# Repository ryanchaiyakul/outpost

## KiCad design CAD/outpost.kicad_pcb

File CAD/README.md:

# CAD

KiCad schematic and board design.

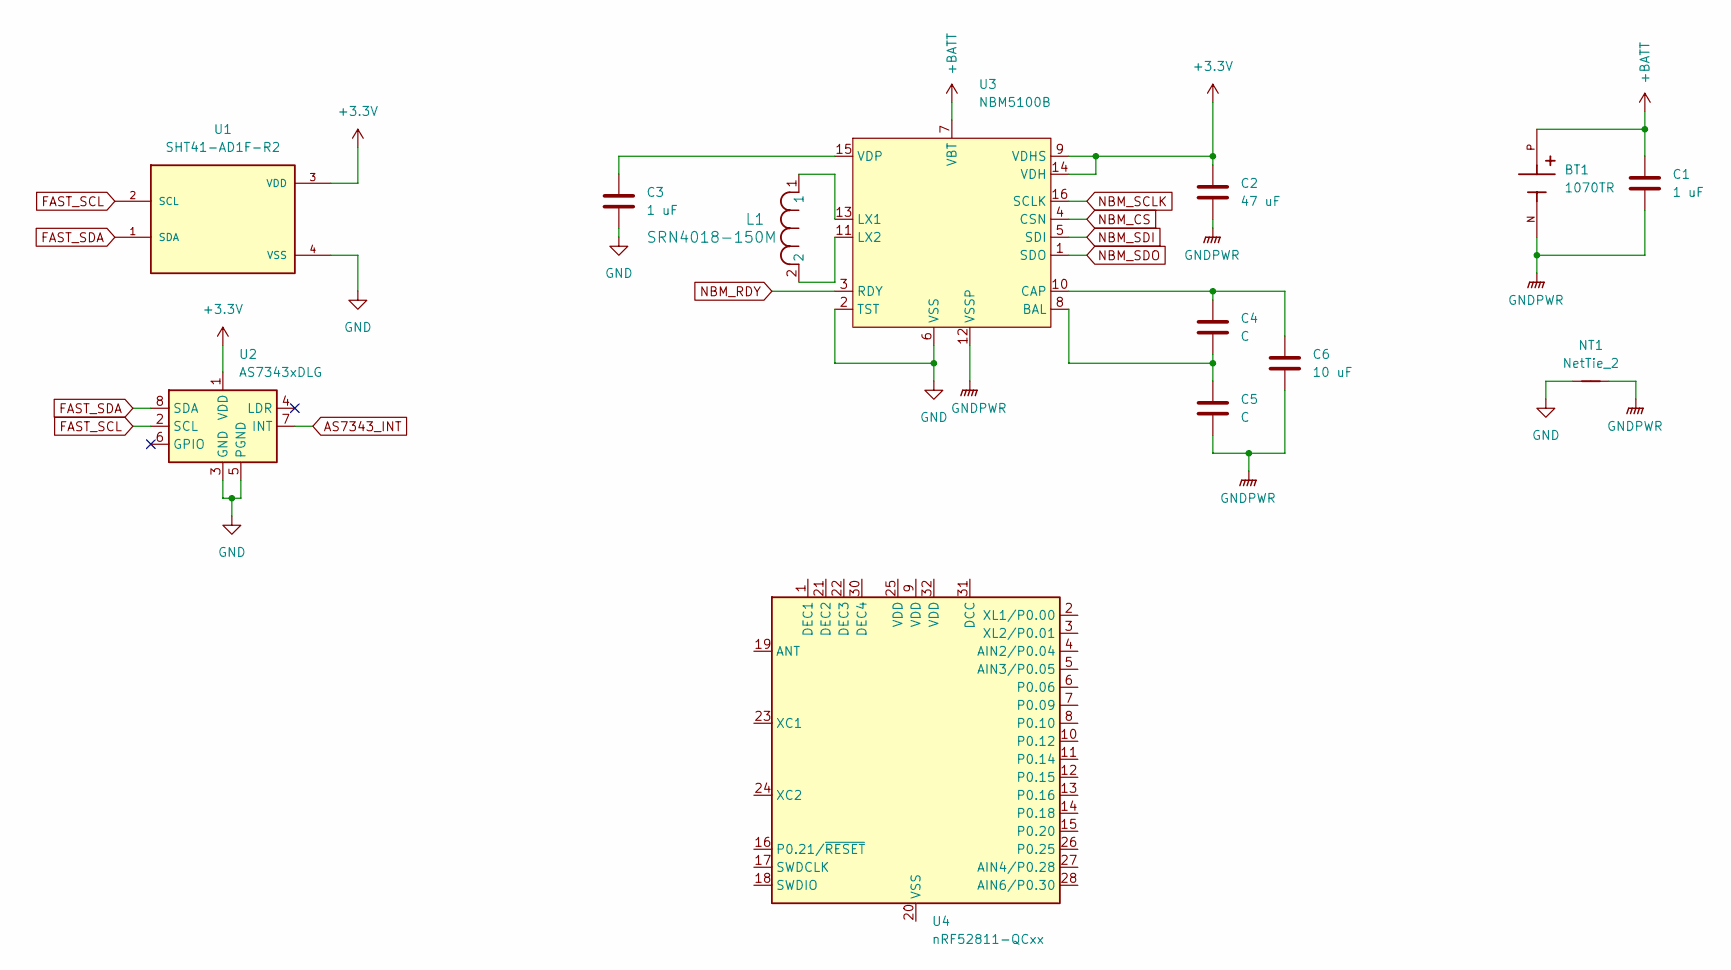
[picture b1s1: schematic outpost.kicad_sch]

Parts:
BT1: 1070TR; KEYSTONE_1070TR; PARTREV C
C1, C3: 1 uF; C_0603_1608Metric_Pad1.08x0.95mm_HandSolder
C2: 47 uF; C_0603_1608Metric_Pad1.08x0.95mm_HandSolder
C4, C5: C; C_0603_1608Metric_Pad1.08x0.95mm_HandSolder
C6: 10 uF; C_0603_1608Metric_Pad1.08x0.95mm_HandSolder
L1: SRN4018-150M; IND_BOURNS_SRN4018
NT1: NetTie_2; NetTie-2_THT_Pad1.0mm
U1: SHT41-AD1F-R2; SHT4X
U2: AS7343xDLG; AMS_OLGA-8_2x3.1mm_P0.8mm
U3: NBM5100B; SOT763-1
U4: nRF52811-QCxx; QFN-32-1EP_5x5mm_P0.5mm_EP3.6x3.6mm_ThermalVias

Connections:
+3.3V: C2.1, U1.3 (VDD), U2.1 (VDD), U3.9 (VDHS), U3.14 (VDH)
+BATT: BT1.P, C1.1, U3.7 (VBT)
AS7343_INT: U2.7 (INT)
FAST_SCL: U1.2 (SCL), U2.2 (SCL)
FAST_SDA: U1.1 (SDA), U2.8 (SDA)
GND: C3.2, NT1.1, U1.4 (VSS), U2.3 (GND), U2.5 (PGND), U3.2 (TST), U3.6 (VSS)
GNDPWR: BT1.N, C1.2, C2.2, C5.2, C6.2, NT1.2, U3.12 (VSSP)
NBM_CS: U3.4 (CSN)
NBM_RDY: U3.3 (RDY)
NBM_SCLK: U3.16 (SCLK)
NBM_SDI: U3.5 (SDI)
NBM_SDO: U3.1 (SDO)
unnamed: C4.2, C5.1, U3.8 (BAL)
unnamed: C4.1, C6.1, U3.10 (CAP)
unnamed: L1.1, U3.13 (LX1)
unnamed: L1.2, U3.11 (LX2)
unnamed: C3.1, U3.15 (VDP)
unnamed: U4.20 (VSS), U4.29 (VSS), U4.33 (VSS)

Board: 2 copper layers, 13 parts (0 on the bottom side), 12 nets, no tracks yet.

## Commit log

2023-12-19 Initial commit for outpost
2023-12-28 removed html files
    Not necessary as the libraries are already included in the KiCad
    settings. Need to verify that the libraries may not be linked properly
    when cloning project.
2023-12-28 Initial GitHub Pages
    Test index.md and _config.yml. Probably will break.
2023-12-28 Update README.md
    Added pages status badge
2023-12-29 Started basic github documentation
2024-01-03 starting as734 docs
    Working on new file structure and website page design. WIP
2024-01-13 updated libraries
    switched to kicad default resistors and capacitors
